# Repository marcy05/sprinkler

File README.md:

# Sprinkler project

This project tracs the sprinkler project.

## Folder structure

1. Hardware

2. Software

3. Documentation

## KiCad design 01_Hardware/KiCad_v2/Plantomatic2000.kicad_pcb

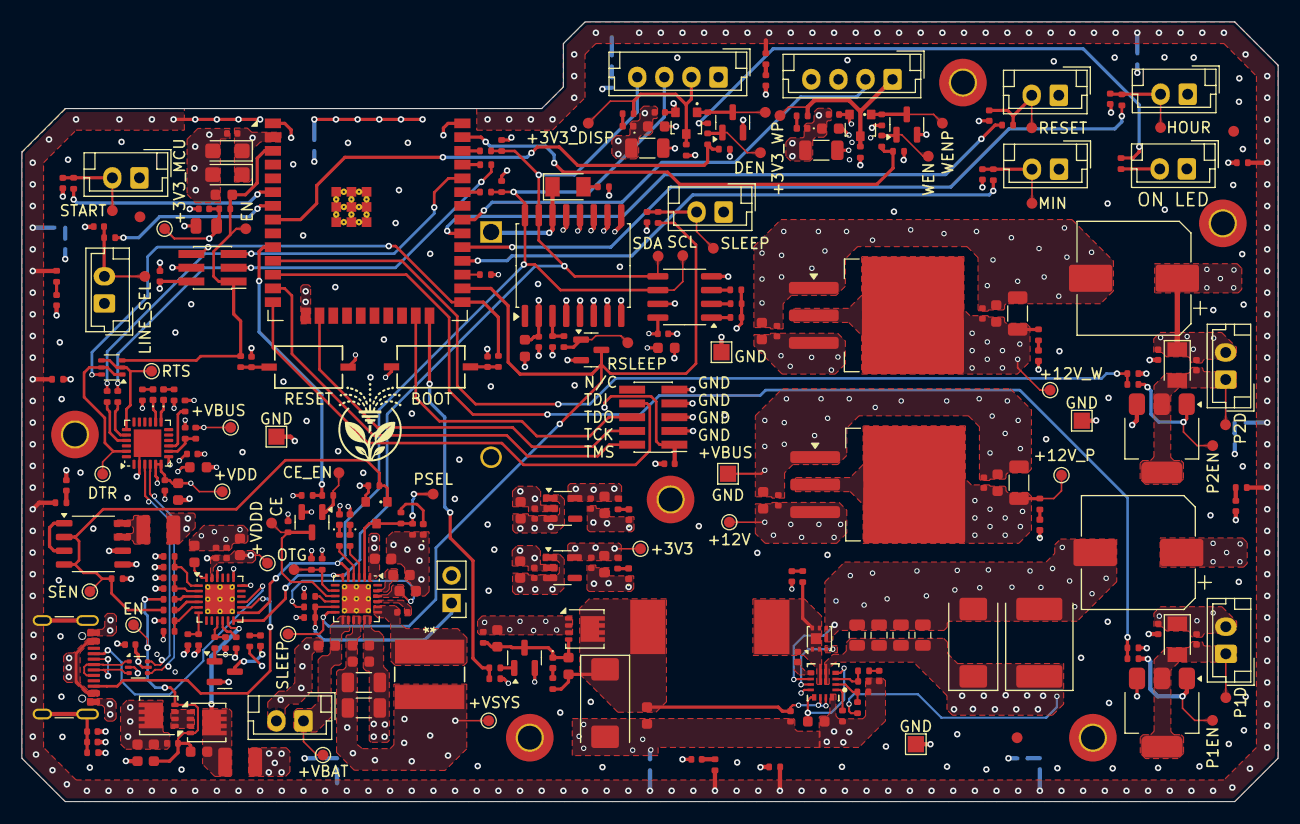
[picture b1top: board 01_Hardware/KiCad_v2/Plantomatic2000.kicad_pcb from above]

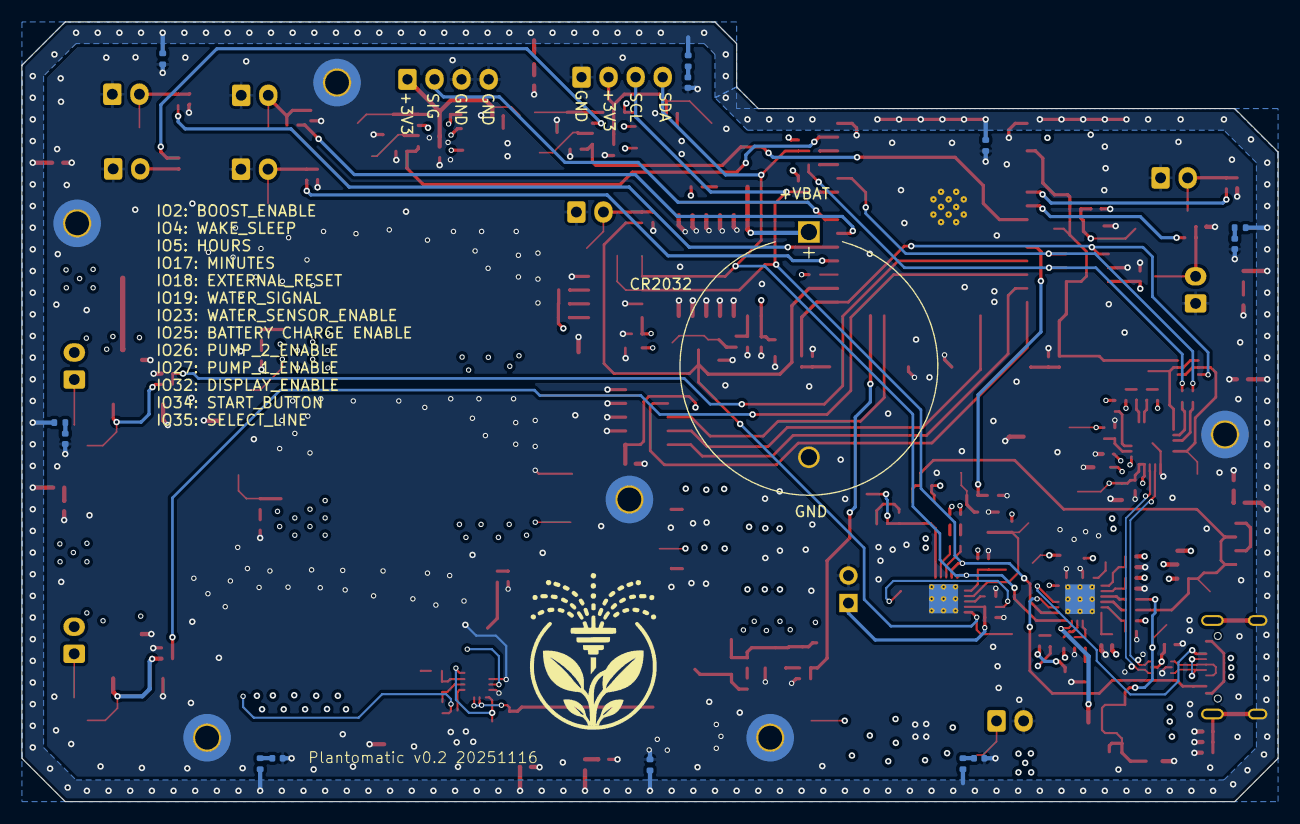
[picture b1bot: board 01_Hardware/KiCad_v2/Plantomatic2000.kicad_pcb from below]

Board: 4 copper layers, 116.0 x 72.0 mm, 322 parts (14 on the bottom side), 144 nets.

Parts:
+3V3, +3V3_MCU, +12V, +12V_P, +12V_W: TestPoint_Small; TestPoint_Pad_D1.0mm
+3V3_DISP, +3V3_WP: TestPoint_Pad_D1.0mm
+VBAT: TestPoint_Small; TestPoint_Pad_D1.0mm
+VBUS: TestPoint_Small; TestPoint_Pad_D1.0mm
+VDD: TestPoint_Small; TestPoint_Pad_D1.0mm
+VDDD: TestPoint_Small; TestPoint_Pad_D1.0mm
+VSYS: TestPoint_Small; TestPoint_Pad_D1.0mm
BT500: BS-07-A1BJ001_CR2032; BatteryHolder_MYOUNG_BS-07-A1BJ001_CR2032
C100, C103, C127, C200, C308: 4.7uF; C_0603_1608Metric
C101, C102, C104, C105, C106, C122, C124, C205, C206, C401, C402, C413, C414, C418, C419, C422, C423, C501, C502, C506, C509, C600, C602, C604, C605, C702, C705, C800, C801, C802, C803, C804, C805, C806, C807, C808, C809: 100nF; C_0402_1005Metric
C123, C301, C302, C303, C307, C400, C403, C412, C415, C417, C420, C421, C424, C505, C508, C701, C704: 10uF; C_0603_1608Metric
C125: 100pF; C_0402_1005Metric
C126, C135: 22nF; C_0402_1005Metric
C128, C129, C130, C131, C132, C133: 47uF; C_1206_3216Metric
C201, C202, C203, C204, C207, C208, C300, C507: 1uF; C_0603_1608Metric
C306: 47nF; C_0402_1005Metric
C404, C405: 330uF; CP_EIA-7343-31_Kemet-D
C406: 470uF; CP_EIA-7360-38_Kemet-E
C407, C408, C409, C410, C411, C416, C425, C426, C427, C428: 4.7nF; C_0402_1005Metric
C500, C510, C511, C512, C513: 22uF; C_0805_2012Metric
C503, C504: 10uF; CP_EIA-3216-18_Kemet-A
C601, C603: 220uF; CP_Elec_10x10
CE: TestPoint_Pad_D1.0mm
CE_EN: TestPoint_Pad_D1.0mm
D100, D101, D300, D302: NCD0402G1; LED_0402_1005Metric
D200, D201, D301, D400, D403, D404, D405, D700, D701: NCD0402R1; LED_0402_1005Metric
D500, D600, D601: SBR3U40S1F; SBR3U40S1F-7
DEN: TestPoint_Pad_D1.0mm
DENP: TestPoint_Pad_D1.0mm
DTR: TestPoint_Small; TestPoint_Pad_D1.0mm
EN: TestPoint_Small; TestPoint_Pad_D1.0mm
EN#2: TestPoint_Pad_D1.0mm
F400, F401: Polyfuse_Small; Fuse_1210_3225Metric
FID400, FID401, FID402: Fiducial; Fiducial_1mm_Mask2mm
GND: TestPoint; TestPoint_Pad_1.5x1.5mm
GND#2, GND#3, GND#4, GND#5: TestPoint; TestPoint_Pad_1.5x1.5mm
H800, H801, H802, H803, H804, H805: MountingHole_Pad; MountingHole_2.2mm_M2_Pad_TopBottom
HOUR: TestPoint_Pad_D1.0mm
J100: TYPE-C-31-M-12; USB_C_Receptacle_GCT_USB4105-xx-A_16P_TopMnt_Horizontal
J300, J600, J601, J801, J802, J803, J805, J806, J807, J808: JST_B2B; JST_EH_B2B-EH-A_1x02_P2.50mm_Vertical
J700, J701: JST_B4B; JST_EH_B4B-EH-A_1x04_P2.50mm_Vertical
J800: Conn_02x03_Odd_Even; PinHeader_2x03_P1.27mm_Vertical_SMD
J804: Conn_02x05_Odd_Even; PinHeader_2x05_P1.27mm_Vertical_SMD
L103: 4.7uH (SPM12565VT-4R7M-D); SPM12565VT-4R7M
L300: SRN6045HA-1R0Y
LINE_SEL: TestPoint_Pad_D1.0mm
MIN: TestPoint_Pad_D1.0mm
OTG: TestPoint_Small; TestPoint_Pad_D1.0mm
P1D, P1EN, P2D, P2EN: TestPoint_Pad_D1.0mm
PSEL: TestPoint_Pad_D1.0mm
Q100: UMH3N; SOT-363_SC-70-6
Q113: CSD17313Q2; Texas_DQK
Q200, Q201, Q204: SI7615DN-T1-GE3; Diodes_PowerDI3333-8
Q202: DMP6050SSD-13; DMP6050SSD_SO-8_3.9x4.9mm_P1.27mm
Q203, Q205, Q301, Q500, Q702, Q703: IRLML2402TRPBF; SOT-23
Q300, Q700, Q701: BSS314PEH6327; BSS314PE
Q600, Q601: STN3NF06L; SOT-223
R100, R112, R308, R700, R702: 22K1; R_0402_1005Metric
R101, R202, R203, R204, R218, R300, R301, R309, R411, R412, R701, R808: 1K; R_0402_1005Metric
R102, R104, R210, R212, R213, R215, R502, R508, R509, R800, R801, R802, R803, R804, R805, R806, R807: 0R; R_0402_1005Metric
R103: 47K5; R_0402_1005Metric
R105, R106, R500: 220R; R_0402_1005Metric
R107, R121, R207, R208, R209, R211, R214, R302, R303, R307, R310, R312, R501, R504, R505, R602, R603, R704, R705, R708, R709: 10K; R_0402_1005Metric
R108: 158K; R_0402_1005Metric
R109: 14K3; R_0402_1005Metric
R110, R201, R216, R217: 49K9; R_0402_1005Metric
R111: 20K; R_0402_1005Metric
R205, R311, R405, R503, R600, R601, R706, R707: 470R; R_0402_1005Metric
R206, R400, R410, R506, R507, R510, R511, R512, R703: 4K7; R_0402_1005Metric
R304: 5K23; R_0402_1005Metric
R305: 130R; R_0402_1005Metric
R306: 30K1; R_0402_1005Metric
R401, R407, R408, R409, R413, R414, R415, R416, R417, R418: 22R; R_0402_1005Metric
R402, R403, R404, R406, R419, R420: 511K; R_0402_1005Metric
RESET: TestPoint_Pad_D1.0mm
RSLEEP: TestPoint_Pad_D1.0mm
RTS: TestPoint_Small; TestPoint_Pad_D1.0mm
SCL: TestPoint_Pad_D1.0mm
SDA: TestPoint_Pad_D1.0mm
SEN: TestPoint_Small; TestPoint_Pad_D1.0mm
SLEEP: TestPoint_Pad_D1.0mm
SLEEP#2: TestPoint_Small; TestPoint_Pad_D1.0mm
START: TestPoint_Pad_D1.0mm
SW800, SW801: SW_Push; SW_101-C-W_XKB
TH300: 103AT-2; PinHeader_1x02_P2.54mm_Vertical
U100: USBLC6-2P6; SOT-666
U101: CP2102N-A02-GQFN24R; CP2102N_QFN-24-1EP_4x4mm_P0.5mm_EP2.5x2.5mm
U104: TPS61287RZPR; RZP0014A-MFG
U200: CYPD3177-24LQ; QFN-24-1EP_4x4mm_P0.5mm_EP2.75x2.75mm_ThermalVias
U300: BQ25892; Texas_RTW_WQFN-24-1EP_4x4mm_P0.5mm_EP2.7x2.7mm_ThermalVias
U403, U404: XC6220B331MR-G; SOT-23-5
U405, U406: LM1085IS-12/NOPB; TO-263-3_TabPin2
U500: DS3231M; SOIC-16W_7.5x10.3mm_P1.27mm
U501: ESP32-WROOM-32E-N4; ESP32-WROOM-32E
U502: AT24CS01-SSHM; SOIC-8_3.9x4.9mm_P1.27mm
WEN: TestPoint_Pad_D1.0mm
WENP: TestPoint_Pad_D1.0mm

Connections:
+3V3: +3V3.1, C132.1, C423.1, C424.1, C701.1, C702.1, Q700.2 (S), R412.1, R704.2, R808.1, U404.5 (VOUT)
+3V3_MCU: +3V3_MCU.1, C419.1, C420.1, C500.1, C501.1, C502.1, C503.1, C504.1, C505.1, C506.1, C508.1, C509.1, R411.1, R500.1, R501.1, R505.1, R506.1, R507.1, R510.1, R511.1, R512.1, U403.5 (VOUT), U500.2 (VCC), U501.2 (VDD), U502.8 (VCC)
+5V: C300.1, F400.2, F401.2, Q300.2 (S), R203.1, R302.1, R310.2, U300.1 (VBUS)
+12V: +12V.1, C400.1, C401.1, C405.1, C406.1, C412.1, C413.1, C510.1, C511.1, C512.1, C513.1, R108.1, U104.5 (VOUT), U405.3 (VI), U406.3 (VI)
+12V_PUMP: +12V_P.1, C130.1, C402.1, C403.1, C600.1, C601.1, C602.1, C603.1, C604.1, C605.1, D600.1 (K), D601.1 (K), J600.2, J601.2, R400.1, U405.2 (VO)
+12V_WATER: +12V_W.1, C131.1, C133.1, C414.1, C415.1, C704.1, C705.1, Q701.2 (S), R410.1, R705.2, U406.2 (VO)
+VBAT: +VBAT.1, C307.1, J300.1, U300.13 (BAT), U300.14 (BAT)
+VBUS: +VBUS.1, C100.1, C101.1, C104.1, C200.1, C201.1, C800.1, C806.1, J100.A4 (VBUS), J100.A9 (VBUS), J100.B4 (VBUS), J100.B9 (VBUS), J800.2, J804.1, Q200.5 (D), Q202.5 (D2), Q202.6 (D2), R100.1, R201.1, R216.1, U100.5 (VBUS), U101.7 (VREGIN), U200.18 (VBUS_IN)
+VDD: +VDD.1, C102.1, C103.1, R101.1, R105.1, R106.1, U101.5 (VIO), U101.6 (VDD)
+VDDD: +VDDD.1, C204.1, C205.1, C206.1, R206.1, R208.1, R209.1, R210.1, R211.1, U200.23 (VDDD)
+VSYS: +VSYS.1, C128.1, C129.1, C207.1, C302.1, C303.1, C417.1, C418.1, C421.1, C422.1, D300.2 (A), D301.2 (A), L300.2, Q204.1 (S), Q204.2 (S), Q204.3 (S), R217.1, R307.1, U300.15 (SYS), U300.16 (SYS), U403.1 (VIN), U403.3 (CE), U404.1 (VIN), U404.3 (CE)
/BATTERY_MANAGEMENT_IC/BTST: C306.2, U300.21 (BTST)
/BATTERY_MANAGEMENT_IC/CE: CE.1, Q301.3 (D), R307.2, U300.9 (~CE)
/BATTERY_MANAGEMENT_IC/ILIM: R305.2, U300.10 (ILIM)
/BATTERY_MANAGEMENT_IC/OTG: OTG.1, R302.2, R303.1, U300.8 (OTG)
/BATTERY_MANAGEMENT_IC/PG: R301.1, U300.3 (~PG)
/BATTERY_MANAGEMENT_IC/PMID: C301.1, U300.23 (PMID)
/BATTERY_MANAGEMENT_IC/PSEL: PSEL.1, Q300.3 (D), R308.1, R309.1, U300.2 (PSEL)
/BATTERY_MANAGEMENT_IC/REGN: C308.1, R304.2, U300.22 (REGN)
/BATTERY_MANAGEMENT_IC/STAT: R300.1, U300.4 (STAT)
/BATTERY_MANAGEMENT_IC/SW: C306.1, L300.1, U300.19 (SW), U300.20 (SW)
/BATTERY_MANAGEMENT_IC/TS: R304.1, R306.2, TH300.1, U300.11 (TS)
/BATTERY_MANAGEMENT_IC/VBUS_FET_SAFE_EN: Q202.2 (G1), Q202.4 (G2), Q300.1 (G), R201.2, R204.1, R310.1, SEN.1
/DC_DC_REGULATORS/BOOST_COMP: C125.1, R110.1, U104.3 (COMP)
/DC_DC_REGULATORS/BOOST_DRV: Q113.3 (G), U104.9 (DRV)
/DC_DC_REGULATORS/BOOST_FB: R108.2, R109.1, U104.2 (FB)
/DC_DC_REGULATORS/BOOST_ILIM: R111.2, U104.1 (ILIM)
/DC_DC_REGULATORS/BOOST_VIN: C123.1, C124.1, C208.1, C404.1, L103.2, Q204.5 (D), R218.1, U104.12 (VIN), U104.13 (EN/UVLO)
/DC_DC_REGULATORS/BOOT: C122.2, U104.7 (BOOT)
/DC_DC_REGULATORS/BOOT_SW: C122.1, L103.1, Q113.1 (D), Q113.2 (D), Q113.5 (D), Q113.6 (D), Q113.8 (D), R121.1, U104.6 (SW)
/DC_DC_REGULATORS/B_VCC: C127.1, U104.4 (MODE), U104.11 (VCC)
/DISPLAY_AND_WATER_ENABLE/3V3_DISPLAY: +3V3_DISP.1, J701.2, Q700.3 (D), R700.1, R701.1
/MICROCONTROLLER/BOOST_EN: R112.1, R405.1, U501.24 (IO2)
/MICROCONTROLLER/CHARGE_EN: R311.1, R312.1, U501.10 (IO25)
/MICROCONTROLLER/DISP_EN: R706.1, R709.1, U501.8 (IO32)
/MICROCONTROLLER/ESP_TXR: R502.2, U501.35 (TXD0/IO1)
/MICROCONTROLLER/HOUR_PIN: R806.1, U501.29 (IO5)
/MICROCONTROLLER/MIN_PIN: R805.1, U501.28 (IO17)
/MICROCONTROLLER/PUMP1_EN: R600.1, R602.1, U501.12 (IO27)
/MICROCONTROLLER/PUMP2_EN: R601.1, R603.1, U501.11 (IO26)
/MICROCONTROLLER/RESET_PIN: R807.1, U501.30 (IO18)
/MICROCONTROLLER/SELECT_LINE_PIN: R803.1, U501.7 (IO35)
/MICROCONTROLLER/START_PIN: R804.1, U501.6 (IO34)
/MICROCONTROLLER/WATER_EN: R707.1, R708.1, U501.37 (IO23)
/MICROCONTROLLER/WATER_SIG: J700.2, U501.31 (IO19)
/PUMPS/PUMP_1_DRAIN: C604.2, D600.2 (A), J600.1, P1D.1, Q600.2 (D), Q600.4 (D)
/PUMPS/PUMP_2_DRAIN: C605.2, D601.2 (A), J601.1, P2D.1, Q601.2 (D), Q601.4 (D)
/USB_C_POWER_DELIVERY/Drain: Q200.1 (S), Q200.2 (S), Q200.3 (S), Q201.1 (S), Q201.2 (S), Q201.3 (S)
/USB_C_POWER_DELIVERY/FAULT: R205.1, R207.1, U200.9 (FAULT)
/USB_C_POWER_DELIVERY/Fuse_1A: F401.1, Q202.7 (D1), Q202.8 (D1)
/USB_C_POWER_DELIVERY/ISNK_COARSE: R210.2, R214.1, U200.5 (ISNK_COARSE)
/USB_C_POWER_DELIVERY/ISNK_FINE: R211.2, R215.1, U200.6 (ISNK_FINE)
/USB_C_POWER_DELIVERY/VBUS_FET_EN: C201.2, C202.2, EN.1, Q200.4 (G), Q201.4 (G), R202.2, R216.2
/USB_C_POWER_DELIVERY/VBUS_MAX: R208.2, R212.1, U200.2 (VBUS_MAX)
/USB_C_POWER_DELIVERY/VBUS_MIN: R209.2, R213.1, U200.1 (VBUS_MIN)
/USB_C_POWER_DELIVERY/VCCD: C203.1, U200.24 (VCCD)
/USB_C_POWER_DELIVERY/fuse_5A: C202.1, F400.1, Q201.5 (D), U200.11 (VDC_OUT)
/USB_C_TO_SERIAL/DTR_SERIAL: DTR.1, Q100.1 (E1), Q100.5 (B2), U101.23 (~DTR)
/USB_C_TO_SERIAL/LED_RX: D101.1 (K), U101.13 (~RXT/GPIO.1)
/USB_C_TO_SERIAL/LED_TX: D100.1 (K), U101.14 (~TXT/GPIO.0)
/USB_C_TO_SERIAL/RST: R101.2, U101.9 (~RST)
/USB_C_TO_SERIAL/RTS_SERIAL: Q100.2 (B1), Q100.4 (E2), RTS.1, U101.19 (~RTS)
/USB_C_TO_SERIAL/SER_RX: R104.2, U101.20 (RXD)
/USB_C_TO_SERIAL/SER_TX: R102.2, U101.21 (TXD)
/USB_C_TO_SERIAL/USB_CONN_D+: J100.A6 (D+), J100.B6 (D+), U100.1 (I/O1)
/USB_C_TO_SERIAL/USB_CONN_D-: J100.A7 (D-), J100.B7 (D-), U100.3 (I/O2)
/USB_C_TO_SERIAL/USB_D+: U100.6 (I/O1), U101.3 (D+)
/USB_C_TO_SERIAL/USB_D-: U100.4 (I/O2), U101.4 (D-)
/USB_C_TO_SERIAL/VBUS_VDIV: R100.2, R103.1, U101.8 (VBUS)
/USB_C_TO_SERIAL/shield: C105.1, C106.1, J100.S1 (SHIELD), R107.1, R401.2, R402.2, R403.2, R404.2, R406.2, R407.2, R408.2, R409.2, R413.2, R414.2, R415.2, R416.2, R417.2, R418.2, R419.2, R420.2
ESP_EN: C507.1, EN#2.1, J800.1, Q100.3 (C2), R501.2, R801.1, U501.3 (EN)
ESP_IO0: J800.6, Q100.6 (C1), R800.1, U501.25 (IO0)
ESP_RX: J800.5, R102.1, U501.34 (RXD0/IO3)
ESP_SCL: J701.3, R506.2, R508.1, SCL.1, U200.13 (HPI_SCL), U300.5 (SCL), U500.16 (SCL), U502.6 (SCL)
ESP_SDA: J701.4, R507.2, R509.1, SDA.1, U200.12 (HPI_SDA), U300.6 (SDA), U500.15 (SDA), U502.5 (SDA)
ESP_TCK: J804.4, U501.16 (IO13)
ESP_TDI: J804.8, U501.14 (IO12)
ESP_TDO: J804.6, U501.23 (IO15)
ESP_TMS: J804.2, U501.13 (IO14)
ESP_TX: J800.3, R104.1, R502.1
GND: BT500.2 (-), C100.2, C101.2, C102.2, C103.2, C104.2, C105.2, C106.2, C123.2, C124.2, C125.2, C126.2, C127.2, C128.2, C129.2, C130.2, C131.2, C132.2, C133.2, C135.2, C200.2, C203.2, C204.2, C205.2, C206.2, C300.2, C301.2, C302.2, C303.2, C307.2, C308.2, C400.2, C401.2, C402.2, C403.2, C404.2, C405.2, C406.2, C407.2, C408.2, C409.2, C410.2, C411.2, C412.2, C413.2, C414.2, C415.2, C416.2, C417.2, C418.2, C419.2, C420.2, C421.2, C422.2, C423.2, C424.2, C425.2, C426.2, C427.2, C428.2, C500.2, C501.2, C502.2, C503.2, C504.2, C505.2, C506.2, C507.2, C508.2, C509.2, C510.2, C511.2, C512.2, C513.2, C600.2, C601.2, C602.2, C603.2, C701.2, C702.2, C704.2, C705.2, C800.2, C801.2, C802.2, C803.2, C804.2, C805.2, C806.2, C807.2, C808.2, C809.2, D302.1 (K), D400.1 (K), D403.1 (K), D404.1 (K), D405.1 (K), D700.1 (K), D701.1 (K), GND.1, GND#2.1, GND#3.1, GND#4.1, GND#5.1, H800.1, H801.1, H802.1, H803.1, H804.1, H805.1, J100.A1 (GND), J100.A12 (GND), J100.B1 (GND), J100.B12 (GND), J300.2, J700.3, J700.4, J701.1, J800.4, J801.1, J802.1, J803.1, J804.3, J804.5, J804.7, J804.9, J805.1, J806.1, J807.1, J808.1, Q113.4 (S), Q113.7 (S), Q203.2 (S), Q205.2 (S), Q301.2 (S), Q500.2 (S), Q600.3 (S), Q601.3 (S), Q702.2 (S), Q703.2 (S), R103.2, R107.2, R109.2, R111.1, R112.2, R207.2, R212.2, R213.2, R214.2, R215.2, R303.2, R305.1, R306.1, R308.2, R312.2, R402.1, R403.1, R404.1, R406.1, R419.1, R420.1, R504.2, R602.2, R603.2, R700.2, R702.2, R708.2, R709.2, SW800.1, SW801.1, TH300.2, U100.2 (GND), U101.2 (GND), U101.25 (GND), U104.8 (PGND), U104.10 (M/SYNC), U104.14 (AGND), U200.19 (GND), U200.22 (GND), U200.25 (GND), U300.17 (PGND), U300.18 (PGND), U300.25 (PGND), U403.2 (GND), U404.2 (GND), U405.1 (GND), U406.1 (GND), U500.4 (~RST), U500.5 (GND), U500.6 (GND), U500.7 (GND), U500.8 (GND), U500.9 (GND), U500.10 (GND), U500.11 (GND), U500.12 (GND), U500.13 (GND), U501.1 (GND), U501.15 (GND), U501.38 (GND), U501.39 (GND), U502.4 (GND), U502.7 (WP)
unnamed: BT500.1 (+), D500.1 (K), U500.14 (VBAT)
unnamed: C126.1, R110.2
unnamed: C135.1, R121.2
unnamed: C407.1, R401.1
unnamed: C408.1, R407.1
unnamed: C409.1, R408.1
unnamed: C410.1, R409.1
unnamed: C411.1, R413.1
unnamed: C416.1, R414.1
unnamed: C425.1, R415.1
unnamed: C426.1, R416.1
unnamed: C427.1, R417.1
unnamed: C428.1, R418.1
unnamed: C801.1, R801.2, SW801.2
unnamed: C802.1, R800.2, SW800.2
unnamed: D100.2 (A), R105.2
unnamed: D101.2 (A), R106.2
unnamed: D200.2 (A), R203.2
unnamed: D200.1 (K), Q203.3 (D)
unnamed: D201.2 (A), R218.2
unnamed: C207.2, C208.2, D201.1 (K), Q204.4 (G), Q205.3 (D), R217.2
unnamed: D300.1 (K), R300.2
unnamed: D301.1 (K), R301.2
unnamed: D302.2 (A), R309.2
unnamed: D400.2 (A), R400.2
unnamed: D403.2 (A), R410.2
unnamed: D404.2 (A), R411.2
unnamed: D405.2 (A), R412.2
unnamed: D500.2 (A), R500.2
unnamed: D700.2 (A), R703.2
unnamed: D701.2 (A), R701.2
unnamed: +3V3_WP.1, J700.1, Q701.3 (D), R702.1, R703.1
unnamed: C803.1, J801.2, R802.2, SLEEP.1
unnamed: C804.1, J802.2, LINE_SEL.1, R803.2
unnamed: C805.1, J803.2, R804.2, START.1
unnamed: C807.1, J805.2, MIN.1, R805.2
unnamed: C808.1, HOUR.1, J806.2, R806.2
unnamed: C809.1, J807.2, R807.2, RESET.1
unnamed: J808.2, R808.2
unnamed: Q202.1 (S1), Q202.3 (S2)
unnamed: Q203.1 (G), R205.2
unnamed: Q205.1 (G), R405.2
unnamed: CE_EN.1, Q301.1 (G), R311.2
unnamed: Q500.1 (G), R503.2, RSLEEP.1
unnamed: P1EN.1, Q600.1 (G), R600.2
unnamed: P2EN.1, Q601.1 (G), R601.2
unnamed: DENP.1, Q700.1 (G), Q702.3 (D), R704.1
unnamed: Q701.1 (G), Q703.3 (D), R705.1, WENP.1
unnamed: DEN.1, Q702.1 (G), R706.2
unnamed: Q703.1 (G), R707.2, WEN.1
unnamed: R206.2, U200.10 (FLIP)
unnamed: R204.2, U200.4 (SAFE_PWR_EN)
unnamed: R202.1, U200.3 (VBUS_FET_EN)
unnamed: R503.1, R504.1, U500.3 (~INT/SQW)
unnamed: R505.2, U501.27 (IO16)
unnamed: R508.2, U501.33 (IO21)
unnamed: R509.2, U501.36 (IO22)
unnamed: R512.2, U502.1 (A0)
unnamed: R511.2, U502.2 (A1)
unnamed: R510.2, U502.3 (A2)
USB_CC1_PD: J100.A5 (CC1), U200.15 (CC1)
USB_CC2_PD: J100.B5 (CC2), U200.14 (CC2)
WAKE_SLEEP: Q500.3 (D), R802.1, SLEEP#2.1, U300.12 (~QON), U501.26 (IO4)

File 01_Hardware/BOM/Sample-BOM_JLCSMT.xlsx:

Comment | Designator | Footprint | JLCPCB Part #（optional）
0R | R102,R104,R210,R212,R213,R215,R502,R508,R509,R800,R801,R802,R803,R804,R805,R806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 | Resistor_SMD:R_0402_1005Metric | C226739
100pF | C125 | Capacitor_SMD:C_0402_1005Metric | C327198
22nF | C135 | Capacitor_SMD:C_0402_1005Metric | C524553
22nF | C126 | Capacitor_SMD:C_0402_1005Metric | C524553
47nF | C306 | Capacitor_SMD:C_0402_1005Metric | C437528
100nF | C101,C102,C104,C105,C106,C122,C124,C205,C206,C401,C402,C413,C414,C418,C419,C422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 | Capacitor_SMD:C_0402_1005Metric | C155422
100nF | C501 | Capacitor_SMD:C_0402_1005Metric | C155422
1uF | C201,C202,C203,C204,C207,C208,C300,C507 | Capacitor_SMD:C_0603_1608Metric | C5673
4.7uF | C100,C103,C127,C200,C308 | Capacitor_SMD:C_0603_1608Metric | C69335
10uF | C123,C301,C302,C303,C307,C400,C403,C412,C415,C417,C420,C421,C424,C505,C508,C701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 | Capacitor_SMD:C_0603_1608Metric | C344022
10uF | C503,C504 | Capacitor_Tantalum_SMD:CP_EIA-3216-18_Kemet-A | C110055
22uF | C500 | Capacitor_SMD:C_0805_2012Metric | C45783
22uF | C510,C511,C512,C513 | Capacitor_SMD:C_0805_2012Metric | C45783
47uF | C128,C129,C130,C131,C132,C133 | Capacitor_SMD:C_1206_3216Metric | C76659
220uF | C601,C603 | Capacitor_SMD:CP_Elec_10x10 | C116211
330uF | C404,C405 | Capacitor_Tantalum_SMD:CP_EIA-7343-31_Kemet-D | C696820
470uF | C406 | Capacitor_Tantalum_SMD:CP_EIA-7360-38_Kemet-E | C600599
130R | R305 | Resistor_SMD:R_0402_1005Metric | C852516
220R | R105,R106,R500 | Resistor_SMD:R_0402_1005Metric | C112291
470R | R205,R311,R405,R503,R600,R601,R706,R707 | Resistor_SMD:R_0402_1005Metric | C114877
1K | R101,R202,R203,R204,R218,R300,R301,R309,R411,R412,R701,R808 | Resistor_SMD:R_0402_1005Metric | C106235
10K | R107,R207,R303,R307,R310,R312,R501,R504,R505,R602,R603,R704,R705,R708,R709 | Resistor_SMD:R_0402_1005Metric | C60490
10K | R121,R208,R209,R211,R214,R302 | Resistor_SMD:R_0402_1005Metric | C60490
20K | R111 | Resistor_SMD:R_0402_1005Metric | C93942
158K | R108 | Resistor_SMD:R_0402_1005Metric | C185464
103AT-2 | TH300 | Connector_PinSocket_2.54mm:PinSocket_1x02_P2.54mm_Vertical | -
14K3 | R109 | Resistor_SMD:R_0402_1005Metric | C226787
22K1 | R100,R112,R308,R700,R702 | Resistor_SMD:R_0402_1005Metric | C852648
30K1 | R306 | Resistor_SMD:R_0402_1005Metric | C850952
4.7uH (SPM12565VT-4R7M-D) | L103 | Custom_Global_Footprints:SPM12565VT-4R7M | -
47K5 | R103 | Resistor_SMD:R_0402_1005Metric | C227098
49K9 | R110,R201,R216,R217 | Resistor_SMD:R_0402_1005Metric | C137969
4K7 | R206,R400,R410,R506,R507,R510,R511,R512,R703 | Resistor_SMD:R_0402_1005Metric | C105871
5K23 | R304 | Resistor_SMD:R_0402_1005Metric | C852857
AT24CS01-SSHM | U502 | Package_SO:SOIC-8_3.9x4.9mm_P1.27mm | MODULE
BQ25892 | U300 | Package_DFN_QFN:Texas_RTW_WQFN-24-1EP_4x4mm_P0.5mm_EP2.7x2.7mm_ThermalVias | C165480
BS-07-A1BJ001_CR2032 | BT500 | Battery:BatteryHolder_MYOUNG_BS-07-A1BJ001_CR2032 | C2979167
BSS314PEH6327 | Q300,Q700,Q701 | Custom_Global_Footprints:BSS314PE | C151506
Conn_02x03_Odd_Even | J800 | Connector_PinHeader_1.27mm:PinHeader_2x03_P1.27mm_Vertical_SMD | -
Conn_02x05_Odd_Even | J804 | Connector_PinHeader_1.27mm:PinHeader_2x05_P1.27mm_Vertical_SMD | -
CP2102N-A02-GQFN24R | U101 | Custom_Global_Footprints:CP2102N_QFN-24-1EP_4x4mm_P0.5mm_EP2.5x2.5mm | C969151
CSD17313Q2 | Q113 | Package_SON:Texas_DQK | C2863837
CYPD3177-24LQ | U200 | Package_DFN_QFN:QFN-24-1EP_4x4mm_P0.5mm_EP2.75x2.75mm_ThermalVias | C2959321
DMP6050SSD-13 | Q202 | Custom_Global_Footprints:DMP6050SSD_SO-8_3.9x4.9mm_P1.27mm | C531158
DS3231M | U500 | Package_SO:SOIC-16W_7.5x10.3mm_P1.27mm | MODULE
ESP32-WROOM-32E | U501 | RF_Module:ESP32-WROOM-32E | C701341
IRLML2402TRPBF | Q203,Q205,Q301,Q500,Q702,Q703 | Package_TO_SOT_SMD:SOT-23 | C2588
JST_B2B | J300,J600,J601,J801,J802,J803,J805,J806,J807,J808 | Connector_JST:JST_EH_B2B-EH-A_1x02_P2.50mm_Vertical | -
JST_B4B | J700,J701 | Connector_JST:JST_EH_B4B-EH-A_1x04_P2.50mm_Vertical | -
LM1085IS-12/NOPB | U405,U406 | Package_TO_SOT_SMD:TO-263-3_TabPin2 | C130908
NCD0402G1 | D100,D101,D300,D302 | LED_SMD:LED_0402_1005Metric | C130723
NCD0402R1 | D200,D201,D301,D400,D403,D404,D405,D700,D701 | LED_SMD:LED_0402_1005Metric | C130719
SBR3U40S1F | D500,D600,D601 | Custom_Global_Footprints:SBR3U40S1F-7
SI7615DN-T1-GE3 | Q200,Q201,Q204 | Package_SON:Diodes_PowerDI3333-8 | C5754591
SRN6045HA-1R0Y | L300 | Custom_Global_Footprints:SRN6045HA-1R0Y
STN3NF06L | Q600,Q601 | Package_TO_SOT_SMD:SOT-223 | C222218
SW_Push | SW800,SW801 | SMD,6x3.6mm | C318938
TPS61287 | U104 | Custom_Global_Footprints:RZP0014A-MFG | C43131394
TYPE-C-31-M-12 | J100 | Connector_USB:USB_C_Receptacle_GCT_USB4105-xx-A_16P_TopMnt_Horizontal | C165948
UMH3N | Q100 | Package_TO_SOT_SMD:SOT-363_SC-70-6 | C62892
USBLC6-2P6 | U100 | Package_TO_SOT_SMD:SOT-666 | C15999
XC6220B331MR-G | U403,U404 | Package_TO_SOT_SMD:SOT-23-5 | C86534
